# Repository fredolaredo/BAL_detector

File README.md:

# BAL_detector

## objectif

recevoir une notification sur ouverture de la boite aux lettre qui se trouve en bas de l'immeuble

fixation par aimant (je ne voulais pas faire de trous dans la BAL et plus facile pour récupérer pour recharger la batterie

basse consommation pour tourner avec une batterie sur plusieurs mois 

## principe

1. ouverture de la porte de la BAL par capteur magnétique

2. envoi d'un packet lora contenant des données ambiantes et le voltage de la batterie

3. notification IFTTT sur message TTN

## composants

atmega328 package DIP28 en 3,3V / 8Mhz

LoRa 1276

DHT22 (pour le fun)

une baterie Lithium 3,7v 1000mAh

un contacteur par effet magnétique

quelques composants passifs : led , resistances, capa de découplage, un push button, ...

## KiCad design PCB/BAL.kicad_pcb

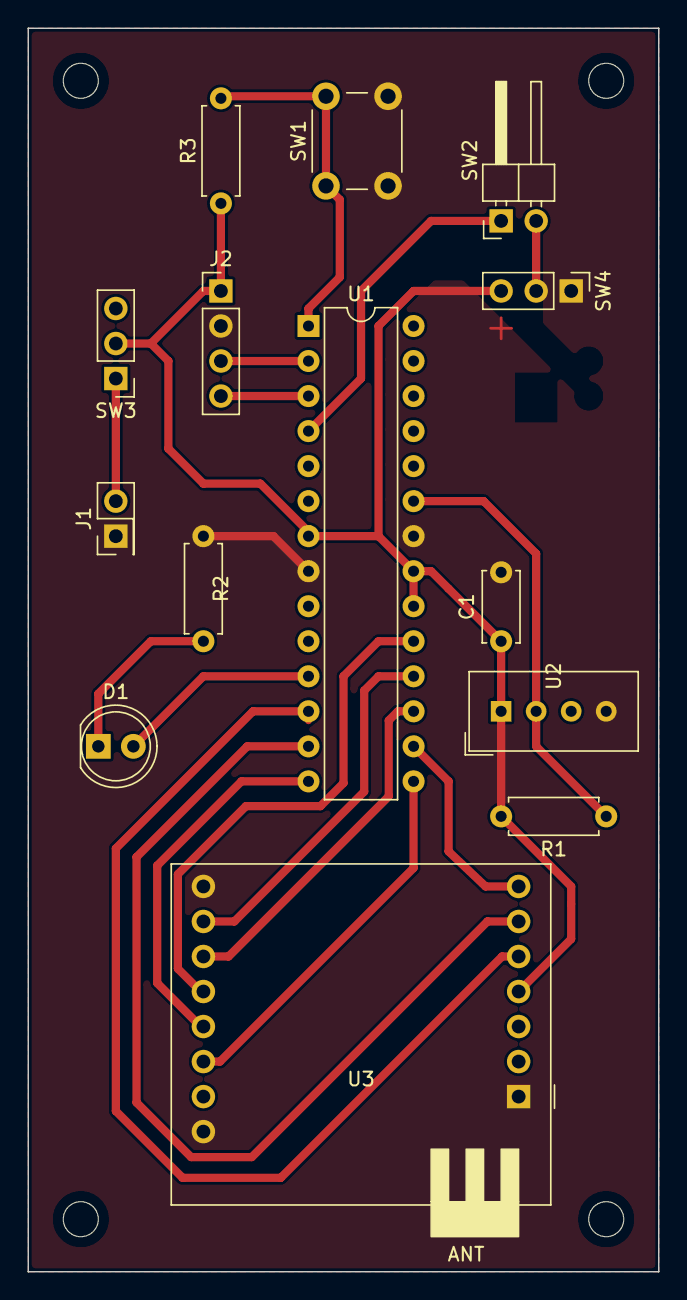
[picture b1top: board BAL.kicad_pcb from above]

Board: 2 copper layers, 45.7 x 90.2 mm, 14 parts (0 on the bottom side), 19 nets.

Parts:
C1: 1nF; C_Disc_D5.0mm_W2.5mm_P5.00mm
D1: LED; LED_D5.0mm
J1: Battery; PinHeader_2x01_P2.54mm_Vertical
J2: UART; PinHeader_1x04_P2.54mm_Vertical
R1, R3: 10k; R_Axial_DIN0207_L6.3mm_D2.5mm_P7.62mm_Horizontal
R2: 180; R_Axial_DIN0207_L6.3mm_D2.5mm_P7.62mm_Horizontal
SW1: SW_Push; SW_PUSH_6mm
SW2: Detecteur; PinHeader_1x02_P2.54mm_Horizontal
SW3: SW_SPST; PinHeader_1x03_P2.54mm_Vertical
SW4: NO/NC; PinHeader_1x03_P2.54mm_Vertical
U1: ATmega328P-PU; DIP-28_W7.62mm
U2: DHT11; Aosong_DHT11_5.5x12.0_P2.54mm
U3: SX1276_package; SX1276_Package

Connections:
+3V3: C1.1, J2.1, R1.2, R3.1, SW3.2, SW4.3, U1.7, U1.20, U1.21, U2.1, U3.4
D0: U1.12, U3.5
D1: U1.13, U3.6
D2: U1.16, U3.7
DATA: R1.1, U1.23, U2.2
GND: C1.2, J1.1, J2.2, R2.1, SW1.2, SW4.1, U1.8, U1.22, U2.4, U3.1, U3.8, U3.15
MISO: U1.18, U3.14
MOSI: U1.17, U3.13
unnamed: D1.1, R2.2
unnamed: D1.2, U1.11
unnamed: J1.2, SW3.1
unnamed: R3.2, SW1.1, U1.1
unnamed: SW2.1, U1.4
unnamed: SW2.2, SW4.2
RST: U1.15, U3.10
RX: J2.4, U1.3
SCK: U1.19, U3.12
SS: U1.14, U3.11
TX: J2.3, U1.2
